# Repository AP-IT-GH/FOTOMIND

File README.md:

## Fotomind 2.0##
 FOTOMIND is a remote to trigger a DSLR camera.
 A Project with Christian Munk, to create a 3D Image by combining multiple simultaneously taken pictures

#Info about the project#

-  Short article about the result of the original project in St. Pölten, Austria
   [Link (Dutch)](http://eaict.ap.be/animation-summer-arduino-interaktiv/)
- All basic information about the FOTOMIND 1.0 project
   [Link](http://www.animationsummer.at/arduino-interaktiv/)
- Site of Christian Munk where he places all his projects.
   [Link](http://www.progressivefactory.com/)
- Article about the collaboration between Artesis Plantijn University College    and St. Pölten University of Applied Sciences
   [Link (Dutch)](https://www.ap.be/nieuws/experiment-met-computer-van-de-toekomst/2178)

Further info can be found in the following folders:

 * 0_administration
 * 1_source
 * 2_hardware
 * 3_documentation
 * 4_presentation

#Groups#

We divided the project in different groups.

- Input
- Output
- Transmission
- Schematic and PCB Design
- Storage pictures

## Youtube##

https://www.youtube.com/watch?v=s_ummqgnZ5k

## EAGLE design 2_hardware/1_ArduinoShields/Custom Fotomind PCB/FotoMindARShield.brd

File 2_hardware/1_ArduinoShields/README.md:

# Arduino shields#

##Schematic:##
We remade and optimized the existing schematic of FotoMind 1.0:
<ul>
<li>Added the wireless connection (nRF24) for remote triggering</li>
<li>Optimized some wire-connections</li>
<li>Added 3 visualisation LEDs to confirm power, trigger, flash,...</li>
<li>Added buttons to test the functionality'On-board' (independent of the wireless-communication)</li>
<li>Added some mulifunctional connectors to add diffrent sensors or outputs</li>
<li>Added a on-board ultrasonic sensor (HC-SR04) to measure distance </li>
</ul>

##The PCB:##
We made a very multifunctional PCB that we easy can adjust by placing/or not placing some components:
<ul>
<li>At the side of the PCD we placed a header the put a distance-sensor (optional)  </li>
<li>In the middle there's a connector to put the wireless-nRF24-module </li>
<li>We have the option to put 3 opto's on the board for trigger(1), Flash and focus</li>
<li>We also have countless options due the multiple connectors connected to the arduino ports and vcc.</li>
</ul>

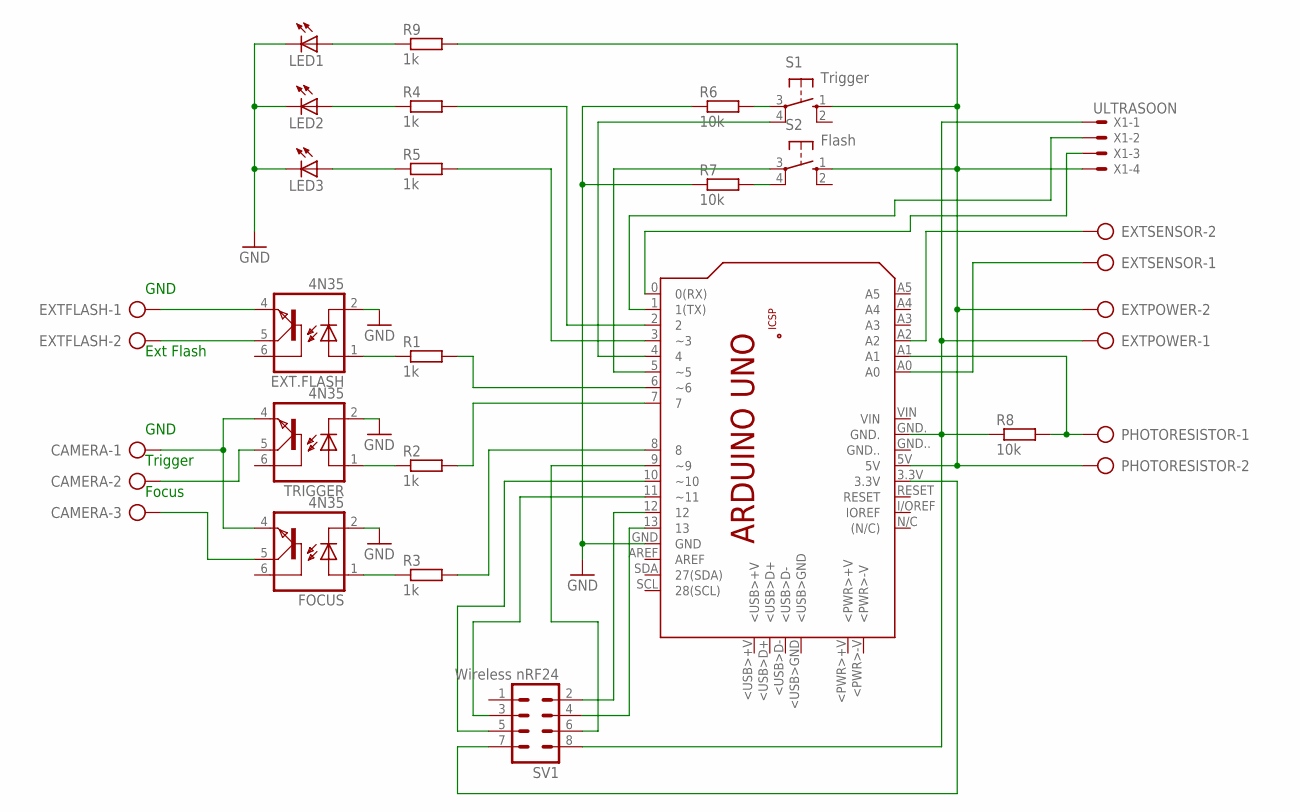
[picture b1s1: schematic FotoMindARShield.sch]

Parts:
CAMERA: AK300/3
EXT.FLASH: 4N35; DIL06
EXTFLASH: AK300/2
EXTPOWER: AK300/2
EXTSENSOR: AK300/2
FOCUS: 4N35; DIL06
LED1, LED2, LED3: LED3MM
PCB1: ARDUINO_UNO
PHOTORESISTOR: AK300/2
R1, R2, R3, R4, R5, R9: 1k; 0204/7
R6, R7, R8: 10k; 0204/7
S1: Trigger; B3F-10XX
S2: Flash; B3F-10XX
SV1: Wireless nRF24; MA04-2
TRIGGER: 4N35; DIL06
X1: ULTRASOON; 22-23-2041

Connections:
GND: EXT.FLASH.2 (C), FOCUS.2 (C), LED1.K (C), LED2.K (C), LED3.K (C), PCB1.GND, R6.1, R7.1, TRIGGER.2 (C)
unnamed: EXT.FLASH.1 (A), R1.1
unnamed: R2.1, TRIGGER.1 (A)
unnamed: FOCUS.1 (A), R3.1
unnamed: PCB1.6 (~6), R1.2
unnamed: PCB1.7, R2.2
unnamed: PCB1.8, R3.2
unnamed: PCB1.2, R4.2
unnamed: PCB1.3 (~3), R5.2
unnamed: LED3.A, R5.1
unnamed: LED2.A, R4.1
unnamed: EXT.FLASH.4 (EMI), EXTFLASH.1
unnamed: EXT.FLASH.5 (COL), EXTFLASH.2
unnamed: CAMERA.1, FOCUS.4 (EMI), TRIGGER.4 (EMI)
unnamed: CAMERA.2, TRIGGER.5 (COL)
unnamed: CAMERA.3, FOCUS.5 (COL)
unnamed: PCB1.4, S1.4 (P1)
unnamed: PCB1.5 (~5), S2.3
unnamed: R6.2, S1.3
unnamed: R7.2, S2.4 (P1)
unnamed: EXTPOWER.1, PCB1.GND., R8.1, SV1.8, X1.1
unnamed: PCB1.A1, PHOTORESISTOR.1, R8.2
unnamed: PCB1.12, SV1.2
unnamed: PCB1.11 (~11), SV1.3
unnamed: PCB1.13, SV1.4
unnamed: PCB1.10 (~10), SV1.5
unnamed: PCB1.9 (~9), SV1.6
unnamed: EXTSENSOR.1, PCB1.A0
unnamed: EXTSENSOR.2, PCB1.A2
unnamed: PCB1.3.3V, SV1.7
unnamed: EXTPOWER.2, PCB1.5V, PHOTORESISTOR.2, R9.2, S1.1 (S), S2.1 (S), X1.4
unnamed: LED1.A, R9.1
unnamed: PCB1.0 (0(RX)), X1.3
unnamed: PCB1.1 (1(TX)), X1.2

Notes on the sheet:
GND
Ext Flash
Trigger
Focus

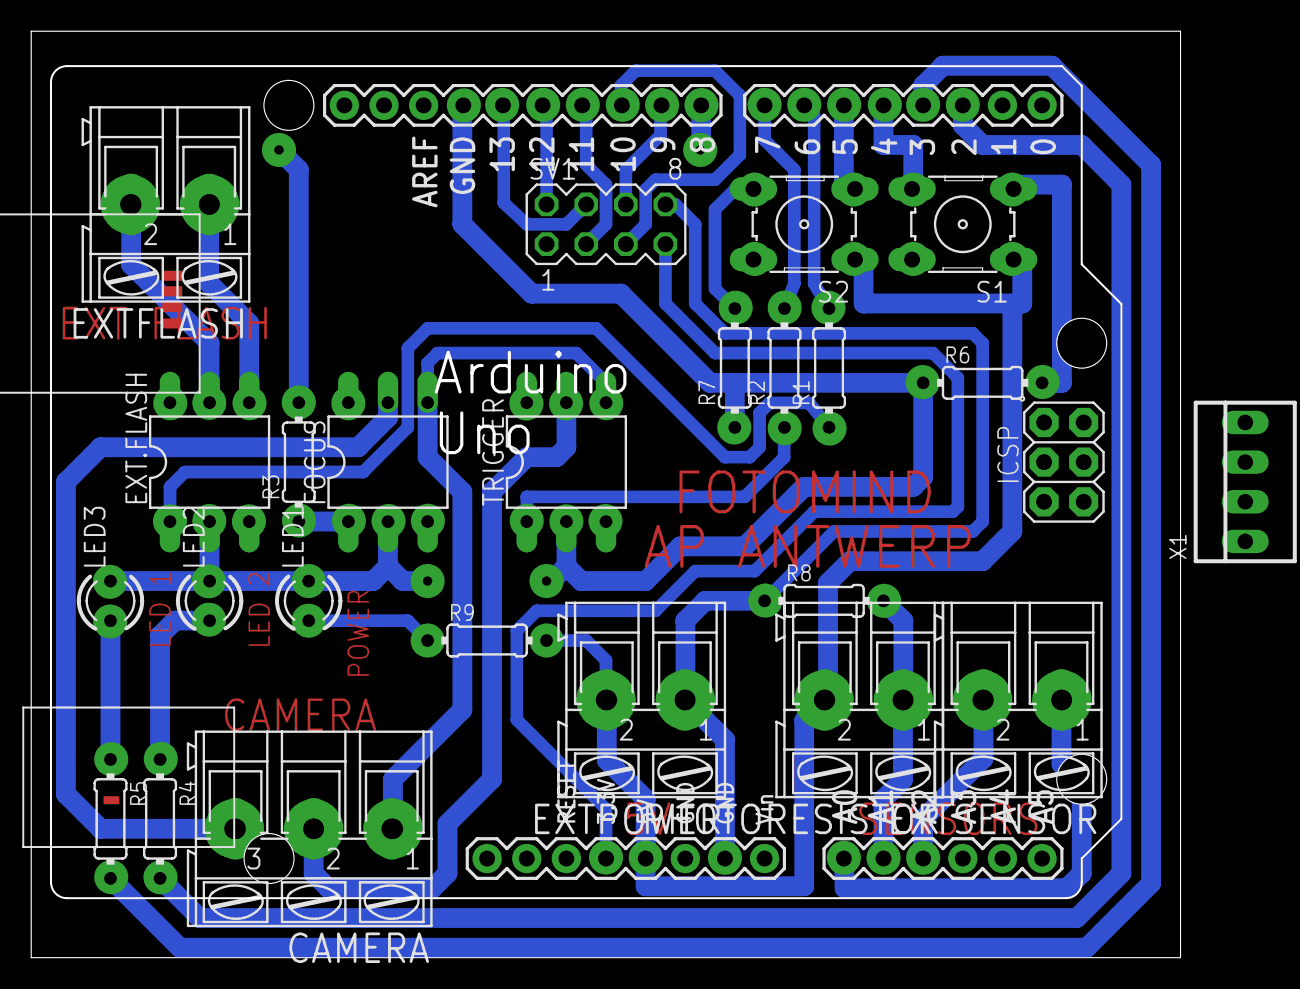
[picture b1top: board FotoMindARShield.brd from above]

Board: 2 copper layers, 73.6 x 59.4 mm, 25 parts (0 on the bottom side), 34 nets.

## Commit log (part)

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2014-11-07 Added folders & placeholders
2014-11-07 Edits to README.md files
2014-11-07 Extra README.md files
2014-11-13 Added links about the project
    Links about the first version of the FOTOMIND.
2014-11-13 Source code first version FOTOMIND
2014-11-13 Added v2.0 folder
    New source folder for FOTOMIND 2.0
2014-11-14 Added High-Level Schematic
    This schematic shows basic high level connectivity
2014-11-19 Edited Lay-out ReadMe
    Edited lay-out of the ReadMe file. Added titles and formated urls.
2014-11-19 Schematics first version added
2014-11-19 Datasheets first version
2014-11-19 Documentation first version PhotoMind
2014-11-20 Updatet High-Level Schematic
2014-11-20 Updatet high level schematic
    master slave added, good schematic use it for project
2014-11-20 Language schematic updatet
    language changed to english
2014-11-20 Arduino master sent data
2014-11-20 Slave Receives Data
2014-11-20 Report session 1
    The report of the session in dutch.
2014-11-20 Update report session 1
    Added code fragments from this session
2014-11-21 Raspberry Pi installation added to README
    This is how we installed the raspberry pi
2014-11-21 Update Photo In 'Verslag'
2014-11-21 Installation of a ramdisk
    ramdisk steps added in README we now have a raspberry pi with up and
    running OS and ramdisk cache
2014-11-21 Install gphoto on raspberry pi README
    using the code in the README we should now be able to connect the
    raspberry pi to a camera. in a later stage this document will be
    'converted' to a script wich will do all this work for you
2014-11-21 Added a beter option for connecting to the Raspberry
    added an other possibility for assigning a static ip for connecting to
    the raspberry pi (user for programming it)
2014-11-21 Allocation Of Duties
    I tried to divide the work in little tasks. Now its up to the group to
    choose who will be doing what and add it to this file.
2014-11-22 Webserver to store pictures taken by camera's
    In this folder are all the files that are used on the webserver to get
    pictures en show them in the browser to simplify delete and save.
2014-11-22 Added upload file to webserver (empty)
2014-11-22 Added libraries to webserver
2014-11-22 Added stylesheet to webserver
2014-11-22 Added icons and fonts to webserver
2014-11-22 Added basic layout to show pictures
2014-11-22 Added some js to activate buttons, imagepicker etc
2014-11-22 Bugfix core js
2014-11-22 Layout readme files changed
2014-11-22 Box Design added to duties
    we should think about how we are going to 'glue' the pieces together
    with as less connections possible
2014-11-22 Added the organization to the README file
2014-11-22 Added structure and layout to startpage
    Added 2 drop boxes, one for selecting the project and the second for
    selecting the camera group
    I also added a title and changed the margin, now it looks better :-)
2014-11-22 Changed 'select' tag to 'id' for init image picker
    In the beginning I used just one multiple select list but now I added 2
    more for selecting the project and group…
2014-11-22 Added file in back-end to get all directories
    this script will return all folders within the DATA directory. It’ll be
    shown in the drop list on the index page.
    Not working yet…
2014-11-22 Example pictures added
    I added these pictures to show the structure of the folders…
2014-11-22 Added script to upload pictures to this server.
    This script will check the extension, check if name is unique and save
    it on the server.
2014-11-22 bug fix readme file
2014-11-23 Shell script made for sending photo to server GetFileFromDirectoryAndSendToServer.sh
    the script now is able to locate the photo and remove it, now i am
    working on uploading the photo to the server
2014-11-23 fixed get_dir
    Get_dir returns an array with all the directories within the root
    folder or in the project folder
2014-11-23 User can select which project and group he want
    This code will get all the directories on the server and place it in a
    list.
2014-11-23 Added exit code to getfile, made startupscript and edited README.md
    Automatic processing should be a fact
2014-11-23 Problem with getting the files from the camera introduced
    must be resolved, we dont know where the pictures are saved
2014-11-23 Display images in current directory
    it’s possible to get all images back from a project in a group on the
    server
2014-11-23 Script to upload images works
2014-11-23 Added upload section to readme file
2014-11-23 Updated readme file
    Deleted some duplicated content
2014-11-24 added .gitignore for visual studio in windows
    gitignore added to 2_windows folder, so graphical interface can be
    created
2014-11-24 Datasheet used optocoupler
2014-11-24 Addded NRF Library for arduino
2014-11-24 Adding Library nRF24
    Library, tests and examples.
2014-11-24 Changed pinlayout in library
2014-11-24 Changed pinlayout
2014-11-24 Fixed connection to camera
    We now have a connection from the raspberrypi to the camera & can upload
    the photo's to the server.
2014-11-24 Remove folder, did not work
2014-11-24 NRF sent, new try with diffrent library
2014-11-24 Added the progress of monday 24/11
    We tested the connection from camera & RaspberryPi & explain how we
    solved some problems.
2014-11-24 Added name to the duties
2014-11-24 nRF24 Receive: code added
2014-11-24 Added sent message
2014-11-24 nRF recieve, works
2014-11-24 Directoty upadated
2014-11-24 Codetest: Sender
2014-11-24 Renamed the report file.
2014-11-24 Added report 2
    Report from 24/11
2014-11-24 Changed in library
2014-11-24 Code increment signal test
2014-11-24 Ultrasonic Sensor Trigger
    Added ultrasonic sensor to trigger SinglePicture() function in
    ArduinoAktive
2014-11-24 Remove void in parameter
2014-11-24 Readme Update
    Added the different groups to the readme file.
2014-11-24 Finale Report Created
    Created the final report with a beautiful lay-out.
2014-11-24 Hex number changed
2014-11-24 Written the report for 24/11
2014-11-24 Added Good Test file for wireless comunication, Cedric will build a library around this
    Changed map structure
2014-11-24 Added extension for raw image file
2014-11-24 Selected pictures can be downloaded in the browser
2014-11-24 Deleted final report docx Created final report md
    On blackboard was mentioned thaht the final report should be available
    as a markdown file.
2014-11-24 Working on the reports
2014-11-24 Start writing library for nFC
2014-11-24 Changed the reports to .md files
2014-11-24 Started writing Final Report
    Added strcuture to the document.
2014-11-24 Basic Build GUI + Arduino Communication Test
    Created a GUI to send commands to Arduino, still has some issues:
    (temporary hardcoded) commands do not show up in listbox yet (binding
    issue)
    Basic implementation for arduino send and receive, open comport etc
    already there.
    Arduino program is just to test connection, no success so far.
2014-11-24 Added my name to members...
2014-11-24 Implemented half of the nRF library so that cedric can use this as a base
    This is not working, we rely on Baellon to get this to work
2014-11-24 Fixed bugs, only save/del picture on select
2014-11-24 Images shown in browser with fixed width
2014-11-24 Added semantic UI components and themes
2014-11-24 Added buttons to UI
    Added button to reload, check and uncheck all images
2014-11-24 separate function for loading images
2014-11-24 Reload images click on btn or after delete images
2014-11-24 Added functionality to toggle selection
2014-11-26 Adjusted Arduino shield
    Changed pins, male to female
2014-11-26 Added report for 26/11/14
    Report with progress added.
2014-11-26 Added 'Readme' for compileproblem
2014-11-26 Added some structure in the arduino source, getting ready for writing the communicationmedium library
2014-11-26 Report 26/11 Continued
2014-11-26 Custom PCB ArduinoShield
2014-11-26 Editing Shield & Adding optocouplers
2014-11-26 Update of UI
    Listbox works, can add new items, show content of command. Items not yet
    saved externally of app, still hardcoded for now. Will start working on
    communication again.
2014-11-26 Updated Final Report
    Description: Fotomind V1.0 updated with information of
    http://www.progressivefactory.com/
2014-11-26 PCB: Converted to 6.3.0 & indication leds
2014-11-26 Added documentation Webserver
2014-11-26 Update to Readme
    Added extra information
2014-11-26 GUI works
    Probably needs to be modified according to needs, but the GUI can turn
    on a led on the arduino. Whiii
2014-11-26 Updated Readme with displayed pictures
2014-11-26 PCB: Added FotoResistor & Testbuttons
2014-11-26 Added BRD-file of PCB
2014-11-26 Removed wrong cpp wilf in CommunicationMedium library
2014-11-26 Updated GUI
    Commands are now being saved to XML file, delete function will be
    implemented next
2014-11-26 Added group to readme
2014-11-26 Remove typo
2014-11-26 Added
2014-11-26 GUI updated, Fully Operational?
    Can delete commands from XML (& listbox) now
2014-11-26 CommunicationTest Updated
    When doing Serial.read, the ASCII character is read, to execute
    command, just compare incomingByte with ascii character.
    Serial.println(incomingByte, DEC) is not necessary to work. GUI does not
    use the returned values (yet?)
2014-11-26 Added NRF24-datasheet
    (Wireless comunication)
2014-11-26 CommunicationMedium is working
    Now it is easy to integrate wireless communication in the project
2014-11-26 Oeps mistakes were made...
2014-11-26 Create gh-pages branch via GitHub
2014-11-27 Fixed Issue introduced by git
2014-11-27 Added header for wireless-nRF24-communication
2014-11-27 Added DistanceLib
2014-11-27 Added Test For Whole setup
    wireless activation, trigger
2014-11-27 Changed standard baudrate
2014-11-27 Edited Distancesensor.cpp
    view range is now max 300 cm
2014-11-27 Show picture in GUI
2014-11-27 Arduino Code For Testing
    Send from computer to arduino master, take picture from sended command
2014-11-27 adjusted Pin numbers
2014-11-27 Corrected Mistake in WirelessTriggerTest.ino
2014-11-27 No Idea Why This Should Be a commit
2014-12-03 Added Requirements + PCB progress
2014-12-03 updatet wireless test bug in receivement of data
2014-12-03 added photo external trigger connector
    to documentation schematics
2014-12-03 PCD completed
2014-12-03 reveicement of data not persistent anymore
2014-12-04 Last lines PCB Shield
2014-12-04 Universal schematic
2014-12-04 New ultrasonic feature
2014-12-05 Final PCB-design, ready to mill ! (+groundplane)
2014-12-05 Added zip-file to mill final pcb
2014-12-09 Script for latest image in folder
    Call last.php to get te latest image in the pre-defined folder.
2014-12-10 Added reports.
2014-12-10 Wirelees Trigger Arduino Sketch implemented piezo. Laser implementation following
2014-12-10 Updated UI
    XML file also created when non-existent
2014-12-10 Added information
2014-12-10 UI update
    can send trigger with my presenter now
2014-12-10 UI update
    btnSend cannot be triggered unless connection with arduino is
    established.
    presenter "next" button triggers manually only
2014-12-10 MIT License added
2014-12-10 Update UI
    Prior button of presenter resets to laser
    added folder results + inserted 2 nice pictures with laser beam visible
2014-12-10 Added laser trigger
2014-12-12 Updatet Structure Added some readme's
2014-12-12 Added ReadMe, schematic and design
2014-12-16 Don't commit JPG files
2014-12-17 TestCode for Multifunctional Shield
2014-12-18 Added code comment and readme
2014-12-18 comment added to communicationmediuym
2014-12-18 changed title of window
    fotomind is sooo much cooler than mainwindow #awesome
2014-12-18 Changed pin number
2014-12-18 Added media (images)
2014-12-18 Revert "Added media (images)"
    This reverts commit d41d37c899311175f419874eeefdc0fbfdc1a064.
2014-12-21 Added images
    (with .gitkeep)
2015-01-09 Added final presentation
2015-01-09 Added possible improvements
2015-01-09 added more improvement Idea's
